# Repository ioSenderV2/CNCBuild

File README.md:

# CNCBuild

The machine, and everything about building, wiring, configuring and instrumenting it. Gantry beams are
**stacked pairs of 8020 `30-6060`** on HGR20 rails and 1605 ball screws.

Written down because these facts kept getting re-derived in conversation - travels, plate dimensions,
what shares a drag chain, which stored setting disagreed with the machine. A firmware fork's scratch
folder was the wrong home for them.

| Folder | What is in it |
|---|---|
| [`machine/`](machine) | The build itself: extrusions, rails, screws, plates, and the mechanical decisions with their reasons |
| [`linear-encoder/`](linear-encoder) | Magnetic linear scales + AS5311 + ESP32-S3 → CAN → grblHAL. The most developed subsystem; design complete, nothing built |
| [`commissioning/`](commissioning) | Measurements taken **from the machine** - travels, squaring, tape extents. The authority when the config disagrees |
| [`wiring/`](wiring) | How the boxes connect - the DB37 between the controller box and the remote axis breakout box |

## Generated views - regenerate, never edit

Three files are built from the prose rather than maintained beside it, because a
hand-maintained summary drifts from what it summarises. That is not hypothetical here: on
2026-10-02 two settled decisions were relitigated, both because a pointer had gone stale.

| Build it with | What you get |
|---|---|
| **`tools\regen.ps1`** | **everything derived, in dependency order, ending with `CNC Build.zip`.** The registry check first, then VALUES/registry.html/fusion CSV, fasteners, the cut list, the 3D model, the shop pack tallies, STATUS and INDEX, the four checkers, then the PDFs - and `make-pdf` bundles the zip on a clean print. `-NoPdf` stops after the checkers and says plainly that the PDFs and the zip are then stale. **This is the one to run**; the rows below are what it calls |
| `python tools/status.py all` | [`STATUS.md`](STATUS.md) - every open item, harvested from the SETTLED: OPEN: FLAG: REJECTED: markers in the prose. [`INDEX.md`](INDEX.md) - every heading in the repo |
| `tools\make-pdf.ps1` | **`docs/build-document.pdf`** - the whole mechanical design as one printable file: the thirteen `machine/*.md` files in reading order, a clickable contents, all fifteen photographs embedded with their captions, and links into the shop pack. ~4.4 MB, 97 pages. **Untracked** - rebuild it, do not commit it |

**If a generated file and a `.md` file disagree, the `.md` file wins** and the generated copy
is stale. The PDF needs two packages - `python -m pip install markdown pillow` - the first to
render the prose, the second to scale the photographs to print size on the way in (22.9 MB of
originals become 4.4 MB of PDF, still over 300 dpi at the size they are printed; the originals
in `machine/photos/` are never touched). `status.py` is stdlib-only on purpose, because it
gates correctness and the PDF does not.

## What lives elsewhere

| | Where | Why |
|---|---|---|
| grblHAL firmware + the CAN plugin | `stevenrwood/iMXRT1062`, branch `srw/local-build-config` | It is firmware and needs that build tree |
| ioSender (the sender application) | `ioSenderV2/ioSender` | Its own product |

## A standing rule for this repo

**The machine is the authority, not the configuration.** `$130` once read 889 mm against a real 860 mm,
because a catalog preset overwrote a measured value - which quietly cost soft-limit protection until it
was found by accident. Anything in `commissioning/` is measured; anything quoted from a config file is
labelled as such.

Datasheets are **committed, not linked**. The ESP32 module's header pinout was extracted once, lost, and
had to be recovered from a schematic - and both of that vendor's URLs refuse a plain fetch. A link is not
a copy.

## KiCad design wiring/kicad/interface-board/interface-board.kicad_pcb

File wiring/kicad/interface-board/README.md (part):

# Interface board - KiCad

The termination board that replaces the DB37 breakout: machine cables in through the
enclosure lid, RP23U5XBB controller fed out the other side. All connectors, no actives -
the 12 V arrives regulated from **its own mains-fed 12 V supply**, on the fourth pair off
the E-stop contactor's block. See
[`../../cabinet-power-and-grounding.md`](../../cabinet-power-and-grounding.md).

> FLAG: **NOT a 36 V -> 12 V buck.** This line said so until 2026-11-05 and it was wrong
> in a way nothing on the board shows: a buck off the motor rail ties logic ground to the
> motor return and throws away the drives' measured per-signal isolation. The board's
> 12 V input connector does not care where the 12 V comes from, so **nothing ordered is
> affected** - only what gets wired into it.

| File | |
|---|---|
| `interface-board.kicad_sch` | The schematic. Symbols are **embedded** (`lib_symbols`), so it needs no external libraries. |
| `interface-board.kicad_pcb` | **REV B, this branch: 133 x 132 mm, FOUR layers** - F.Cu signal, In1.Cu solid GND plane, In2.Cu solid +12V plane, B.Cu signal, plus the 36 V pours. 27.2 sq in. **Top half MACHINE IN, bottom half RP23 OUT.** The lid gets cut to match the board. The four M3 holes are **at the corners** - 22,4 / 125,4 / 5,127.3 / 127,127.3 from the top-left; [`../../../docs/drawings/board-mounting.html`](../../../docs/drawings/board-mounting.html) is the drilling drawing and regenerates from this file. **main still holds Rev A** (210 x 94, 2 layers) - the boards in hand. |
| `interface-board.pretty/` | Project footprints for the two parts KiCad's libraries lack: the 85508 jack and the 3P single-row header, both taken from the committed Molex drawings. |
| `route.py` | Regenerates ALL copper from the placed footprints - the Rev B rewrite of the channel router. Owns every track on the board; re-run it after moving a part, then refill zones via the DRC command below. GND and +12V are inner-plane zones and route themselves (every pad on both nets is through-hole); signals run as F.Cu verticals into three packed B.Cu lane corridors. Verticals cross a connector row on searched columns, 0.70 mm apart - track-past-via, not just track-track - with jogs in the gap above the row. |
| `fab/oshpark/` | Manufacturing outputs for **OSH Park**: gerbers (Protel extensions), Excellon drill, and `interface-board-oshpark.zip` - the one file their upload takes. Board is 210 x 94, 2 layers; their standard 1.6 mm matches the 85508 jack's 1.57 tooling. **Rev A ordered 2026-11-03**, OSH Park order xPBWS3rt, $164.95 for 3 with FedEx 2 Day - this zip is what was uploaded; invoice alongside. Regenerate after any board change with the two kicad-cli export commands, then re-zip. |
| `fab/oshpark-revb/` | **Rev B manufacturing outputs - FOR A QUOTE, NOT AN ORDER.** `interface-board-revb-oshpark.zip` is the single file their upload takes: 13 files, all four copper layers (`.gtl` `.g1` `.g2` `.gbl`), masks, silks, `.gm1` outline and the Excellon drill. The drill **map** is written alongside but deliberately kept **out of the zip** - it is a `.gbr` and their uploader can mistake it for a copper layer. Outline measured from the plotted gerber: **x 5..138 by y 5..137 - 133.00 x 132.00 mm, 27.2 sq in.** Regenerate after any board change **with `make-fab-revb.ps1`**, which keeps the refill and the map-exclusion from being forgotten. **Rev A's order record in `fab/oshpark/` is not touched by this.** |
| `silk.py` | Regenerates every free silkscreen label (function names, per-terminal signal names). Owns all board text - edit its tables, not the board. |
| `interface-board.kicad_pro` | Project wrapper. |
| `netlist.txt` | The connection list. **Generated from the routed board by `make-netlist.py`** - not hand-kept, and not from the seed. |
| `make-netlist.py` | Writes `netlist.txt` from the board. Run after any net change. |
| `make-fab-revb.ps1` | Builds the whole Rev B quote package - DRC with refill, both exports, the zip. Refuses to build if DRC is not clean. Run this rather than the export commands by hand. |
| `swap-power-connectors.py` | Placed the three cabinet power feeds as Mini-Fit Jr. Kept because it carries the courtyard arithmetic for row A, which is the tightest row on the board. |
| `generate.py` | **The seed that produced the first version - not the live source once KiCad has touched the file.** See the warning below. |

> FLAG: **`generate.py` is a SEED, not the source of truth once the schematic has been
> opened and re-saved by KiCad.** Re-running it overwrites hand edits and layout work.
> Same rule as the two linear-encoder boards. If the design changes, edit in Eeschema.
>
> FLAG: **AND `netlist.txt` IS NO LONGER ITS OUTPUT.** It used to be, which meant the
> only way to refresh the netlist was to run the seed - which would have destroyed the
> board. So it was hand-edited instead, and had already lost its trailer that way.
> `make-netlist.py` now derives it from the routed board, and
> `drc --schematic-parity` is what makes "from the board" and "from the schematic" the
> same statement.

## What is on it

| Machine side (top-entry, through the lid) | Controller side |
|---|---|
| 5x RJ45 vertical, one cat6 per stepper - column order **X, Y1, Y2, Z, B**, each with its limit 3P stacked below it | 2x10 IDC ribbon to RP23 **J20** (pin-for-pin), right end of the board |
| Mini-Fit Jr 3P - 3D probe (12 V), 3P - toolsetter (12 V) | 2x3 IDC ribbon to RP23 **J24** servo alarms, left end |
| 2x Mini-Fit Jr 2P - touch probes | Mini-Fit Jr 2P - 12 V IN, Mini-Fit Jr 2P - 12 V OUT to the RP23, Mini-Fit Jr **4P - 36 V IN from the supply, both legs doubled** - the three cabinet feeds side by side, all latched so a pulled feed has no bare conductor |
| **5x Mini-Fit Jr 2P - stepper power**, one per axis under its limit connector: where the **18/2** motor supply cable terminates. Pin 1 **+36 V**, pin 2 **return** | |
| 2x Mini-Fit Jr 2P - mist, flood | 3.5 mm TBs, one position per signal with silk names: limits 5P, spindle 4P, probe + door 2P |
| Mini-Fit Jr 4P - spindle (Enable, GND, GND, 0-10 V) | 3.5 mm TBs passing the new inputs through: mist 2P, flood 2P, control 4P; UART1 leaves on a **1x4 2.54 mm header** - dupont jumpers straight to the RP23's 4-pin UART header |
| Mini-Fit Jr 4P - cycle start / feed hold / e-stop / spare | 5x 2.54 mm header, **GND / Step / Dir / Enable** per axis - jumper to a Teensy T41U5XBB instead of the ribbon |
| Mini-Fit Jr 4P - UART1 for CAN, **TX / RX / 3.3V / GND** | |

**Y1 drives the controller's Y, Y2 drives A.** The three touch/3D probe signals are
wired-OR onto one PROBE net; the toolsetter goes to DOOR. Mist, flood, control and
UART1 pass straight through, connector to output terminal, position for position -
UART1's output being the 1x4 header rather than a screw block.

**RJ45 pin map** (striped conductor = signal, solid = return):
1 Step, 3 Enable, 5 Dir, 7 Alarm; evens GND. Step and Alarm sit on opposite edges of
the jack - Step is the aggressor and Alarm feeds EStop. Signals on odds is correct on
the twists by construction: in T568 every odd pin's twist partner is an even pin.

**"Evens GND" does not say WHICH even pin, and that is where a split pair comes from.**
The twists are **1-2, 3-6, 4-5, 7-8**. So each signal's return leg must land on its
own twist partner: Step 1-2, Enable **3-6**, Dir **5-4**, Alarm 7-8. Wiring it as the
numbers read - 3 with 4, 5 with 6 - puts Enable and Dir in each other's twists. The
board cannot catch it, because all four evens are the same GND net: it passes
continuity and works, and costs only signal integrity. Drive-end terminals and the
reasoning are in [`../../ig57-drives.md`](../../ig57-drives.md).

**3P pin order**: 1 = 12 V, 2 = signal, 3 = GND - matches the SN04's brown/black/blue.

🔴 **THE 36 V PAIR IS ISOLATED AND MUST STAY THAT WAY.** `+36V` and `36V_RET`
touch nothing else on the board - not GND, not +12V. That is the same rule the
12 V supply exists to protect: tying the motor return to logic ground throws away
the drives' measured per-signal isolation. **The 36 V return is not a ground.**

**THIS BOARD HAS NO PE CONNECTION AT ALL, AND THAT IS DELIBERATE.** There is no earth
or chassis net on it - 44 nets, none of them PE - **all four mounting holes are
unplated NPTH with no net**, and its enclosure is 3D printed, so there is no chassis
to bond. **Its GND arrives on one pad, J18.2 of the 12 V IN connector**, and leaves on
J19.2 to the RP23. The In1 plane distributes it from there.

✅ **THE TWO RULES ARE THE SAME RULE: SEPARATE EVERYWHERE, JOINED AT ONE POINT.** Logic
GND and the 36 V return do meet - **back at the cabinet's PE bar**, which carries
*12 V supply 0 V* and *motor supply 0 V* as two of its eight named conductors, see
[`../../cabinet-power-and-grounding.md`](../../cabinet-power-and-grounding.md).
**That bar is the single point, and the board staying isolated is what keeps it
single.** A second meeting anywhere - a jumper here, a shared terminal out at a
drive - turns one bond into a loop and puts chopped motor return current through
the logic ground plane. 🔴 **So do not "helpfully" tie `36V_RET` to GND anywhere.**

**The 36 V bus is copper pours, not traces, and that is what set the board size.**
The supply is 600 W at 36 V - **16.5 A across all axes**, nameplate, see
[`../../breakout-box.md`](../../breakout-box.md) - and 16.5 A wants about 10 mm of
1 oz copper per leg. Under the limit row **both legs are on B.Cu**, stacked, because
F.Cu in that band belongs to the five signal bundle streets that have to cross it;
down the east edge **+36V takes F.Cu and 36V_RET takes B.Cu** in one 10.2 mm channel,
stitched with 20 vias where +36V changes layer. [`route.py`](route.py) owns all of it.

**J20 is a skipped reference.** On this bench "J20" means the RP23's stepper header;
two J20s in one enclosure invites miswiring.

## Status: verified against KiCad 10.0.5

| Check | Result |
|---|---|
| ERC, error severity | **0 violations** |
| `netlist.txt` | **All 44 nets**, planes included, written straight from the kicad-cli export. FLAG: **this is no longer an independent check.** It was one while `generate.py` produced both; now that KiCad owns the schematic the file can only be derived from it, so it is documentation, not corroboration. |
| PCB DRC with schematic parity, error severity | **0 violations, 0 unconnected, 0 parity issues** |

Reproduce with:

```
kicad-cli sch erc --severity-error --exit-code-violations interface-board.kicad_sch
kicad-cli sch export netlist --format kicadsexpr --output kicad-export.net interface-board.kicad_sch
kicad-cli pcb drc --schematic-parity --severity-error --exit-code-violations --refill-zones --save-board interface-board.kicad_pcb
```

## Open items

1. **J17 alarm pin -> RP23 LED mapping.** All five alarm pins join one net on the RP23,
   so the wiring works regardless; which pin lights which axis LED is unlabelled in the
   RP23 schematic. Read the board silkscreen when making the ribbon.
2. **Footprints.** All 41 assigned and the board is placed and routed. The IDC headers
   are the standard shrouded 2.54 mm pattern (any vendor fits); the signal terminal
   blocks are 3.5 mm on the 4Ucon pattern (KF350 class fits), and the **three cabinet
   power feeds** - 12 V in, 12 V out and 36 V in - are **Mini-Fit Jr**, the same family
   as the five stepper power jacks above them. Board-side parts:

   | Position | Part | Qty |
   |---|---|---|
   | RJ45 vertical (J1-J5) | Molex **85508-5001** - top entry, THT, Cat5e, shielded (tab to GND; the patch cables are UTP so it carries nothing), no magnetics, 16.85 mm tall. 10 ordered 2026-11-03, Mouser order 40971773. NOT the sensor board's jack - that stays the unshielded 69255-004LF, whose end must float | 5 |
   | 3P single row (J6-J12) | Molex **39-30-1039** - 5566, vertical, peg lock. 20 ordered 2026-11-03, Mouser order 40971773 | 7 |
   | 4P dual row 2x2 (J15, J32, J33, **J55 36 V in**) | Molex **46999-0621** - 2x2 vertical, tin, 10 ordered 2026-11-02, Mouser order 40971389. **J55 is the 36 V input and uses all four circuits for two conductors**: pins 1+2 are both `+36V`, pins 3+4 are both `36V_RET`. Two crimps per leg in the cable, not one | 4 |
   | 2P dual row (J13, J14, J30, J31, **J18 12 V in, J19 12 V out**, **J50-J54 stepper power**) | Molex **39-29-9027** - 2 ckt vertical with peg, tin, 10 ordered 2026-11-02, Mouser order 40971389 (the same order's 39-31-0027 is 10 spare 2-ckt without peg - they also fit these footprints). The four probe/mist/flood positions carry signal; **the five power positions carry 5 A each** - Mini-Fit Jr is rated 9 A on 18 AWG, so the part is the same and the crimp terminal is what must suit the wire. **11 positions against 10 pegged parts in hand** - covered by the 10 pegless 39-31-0027 from the same order, which fit this footprint; the peg is worth keeping on the feeds that get unplugged | 11 |
   | 3.5 mm TB 2P (J23, J34, J35) | KF350-class screw block, 4Ucon pattern - **to order** | 3 |
   | 3.5 mm TB 4P (J22, J36) | same family - **to order** | 2 |
   | 3.5 mm TB 5P (J21) | same family - **to order** | 1 |
   | Pin header 1x04 2.54 mm (J40-J44, J37 UART1 out) | any breakaway header - **to order or from stock** | 6 |

   Cable-end housings (5557, take the 5556 terminals already in stock): 3P single row
   **39-01-4031**, 4P single row **39-01-4041**, 2P dual row **39-01-2025** family.
   There is no 2P in the 5566 single-row range - it starts at 3 circuits, which is why
   the touch probes are dual-row and self-key by shape against the 3P sockets.

   NOTE: **THE THREE CABINET FEEDS NOW NEED CABLE-END HOUSINGS, WHICH SCREW BLOCKS DID
   NOT.** Two more 2P dual-row for the 12 V pair and one more 4P for the 36 V input -
   and the 36 V one takes **four** crimp terminals for its two conductors. That is the
   ordering consequence of the connector change and it is the only one.
3. **RP23 header state, from his board in hand:** J24 already carries a bare 2x3 header;
   J20 is open with plenty of room, so it gets a **shrouded** 2x10 (Digi-Key: CNC Tech /
   On Shore class, 2.54 mm vertical THT). The alarm ribbon's RP23 end therefore lands on
   an unkeyed header - mark pin 1 against the silkscreen; this board's J17 can still be
   shrouded so the interface end is foolproof.

---

## Rev B - designed on this branch, 2026-11-09

**His call, 2026-11-09: "proceed with this alternate design and see how it shakes out."**
This branch is that design, done: placed, routed, ERC/DRC clean, silkscreened, mounting
sheet regenerated. 🔴 **THE FAB STILL WAITS** until Rev A's lessons are in - no order goes
out on the back of this branch alone.

### What it came out as

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
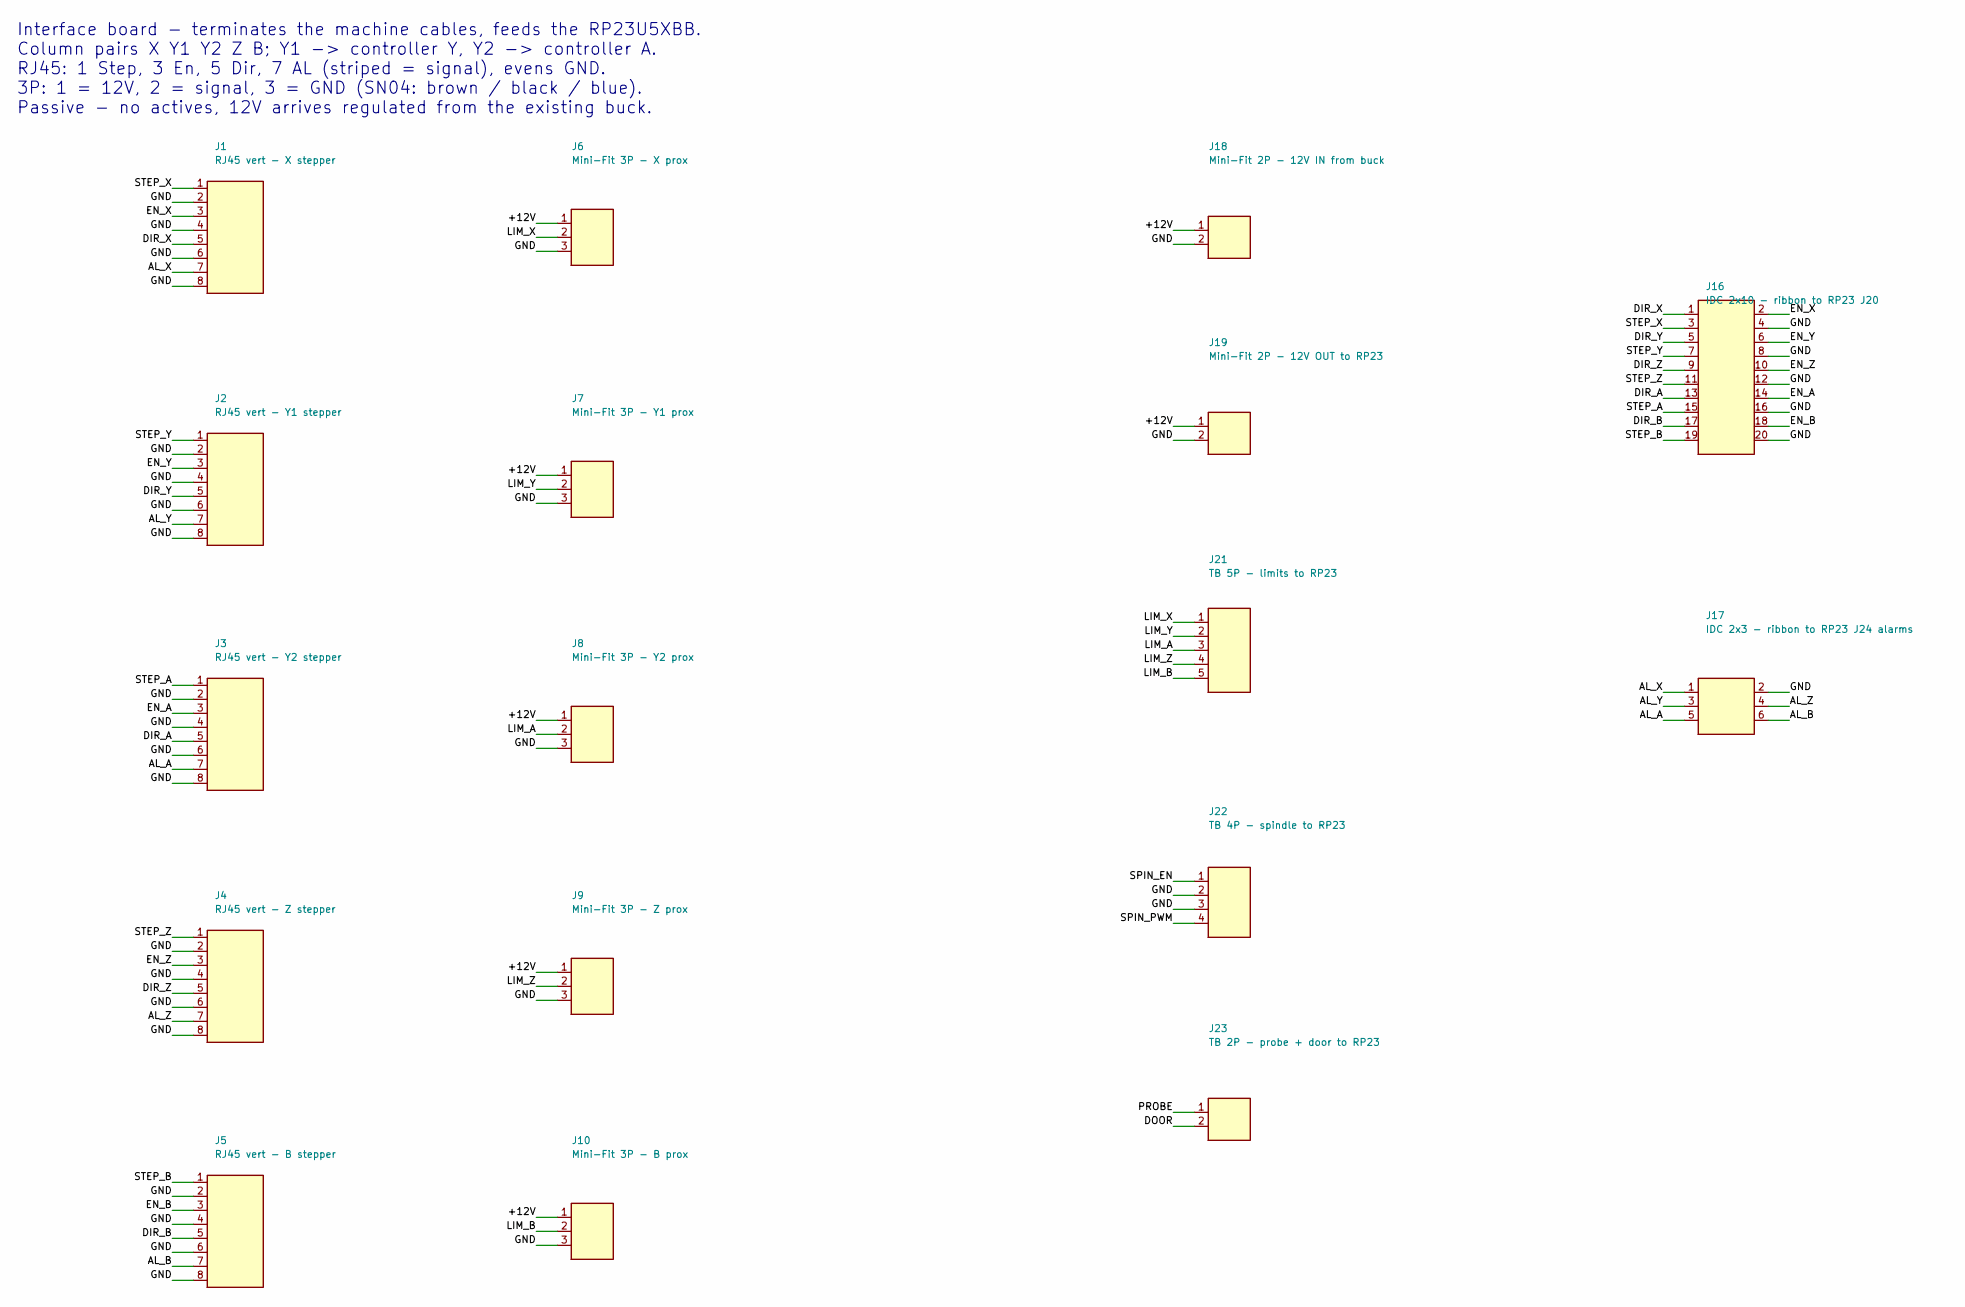
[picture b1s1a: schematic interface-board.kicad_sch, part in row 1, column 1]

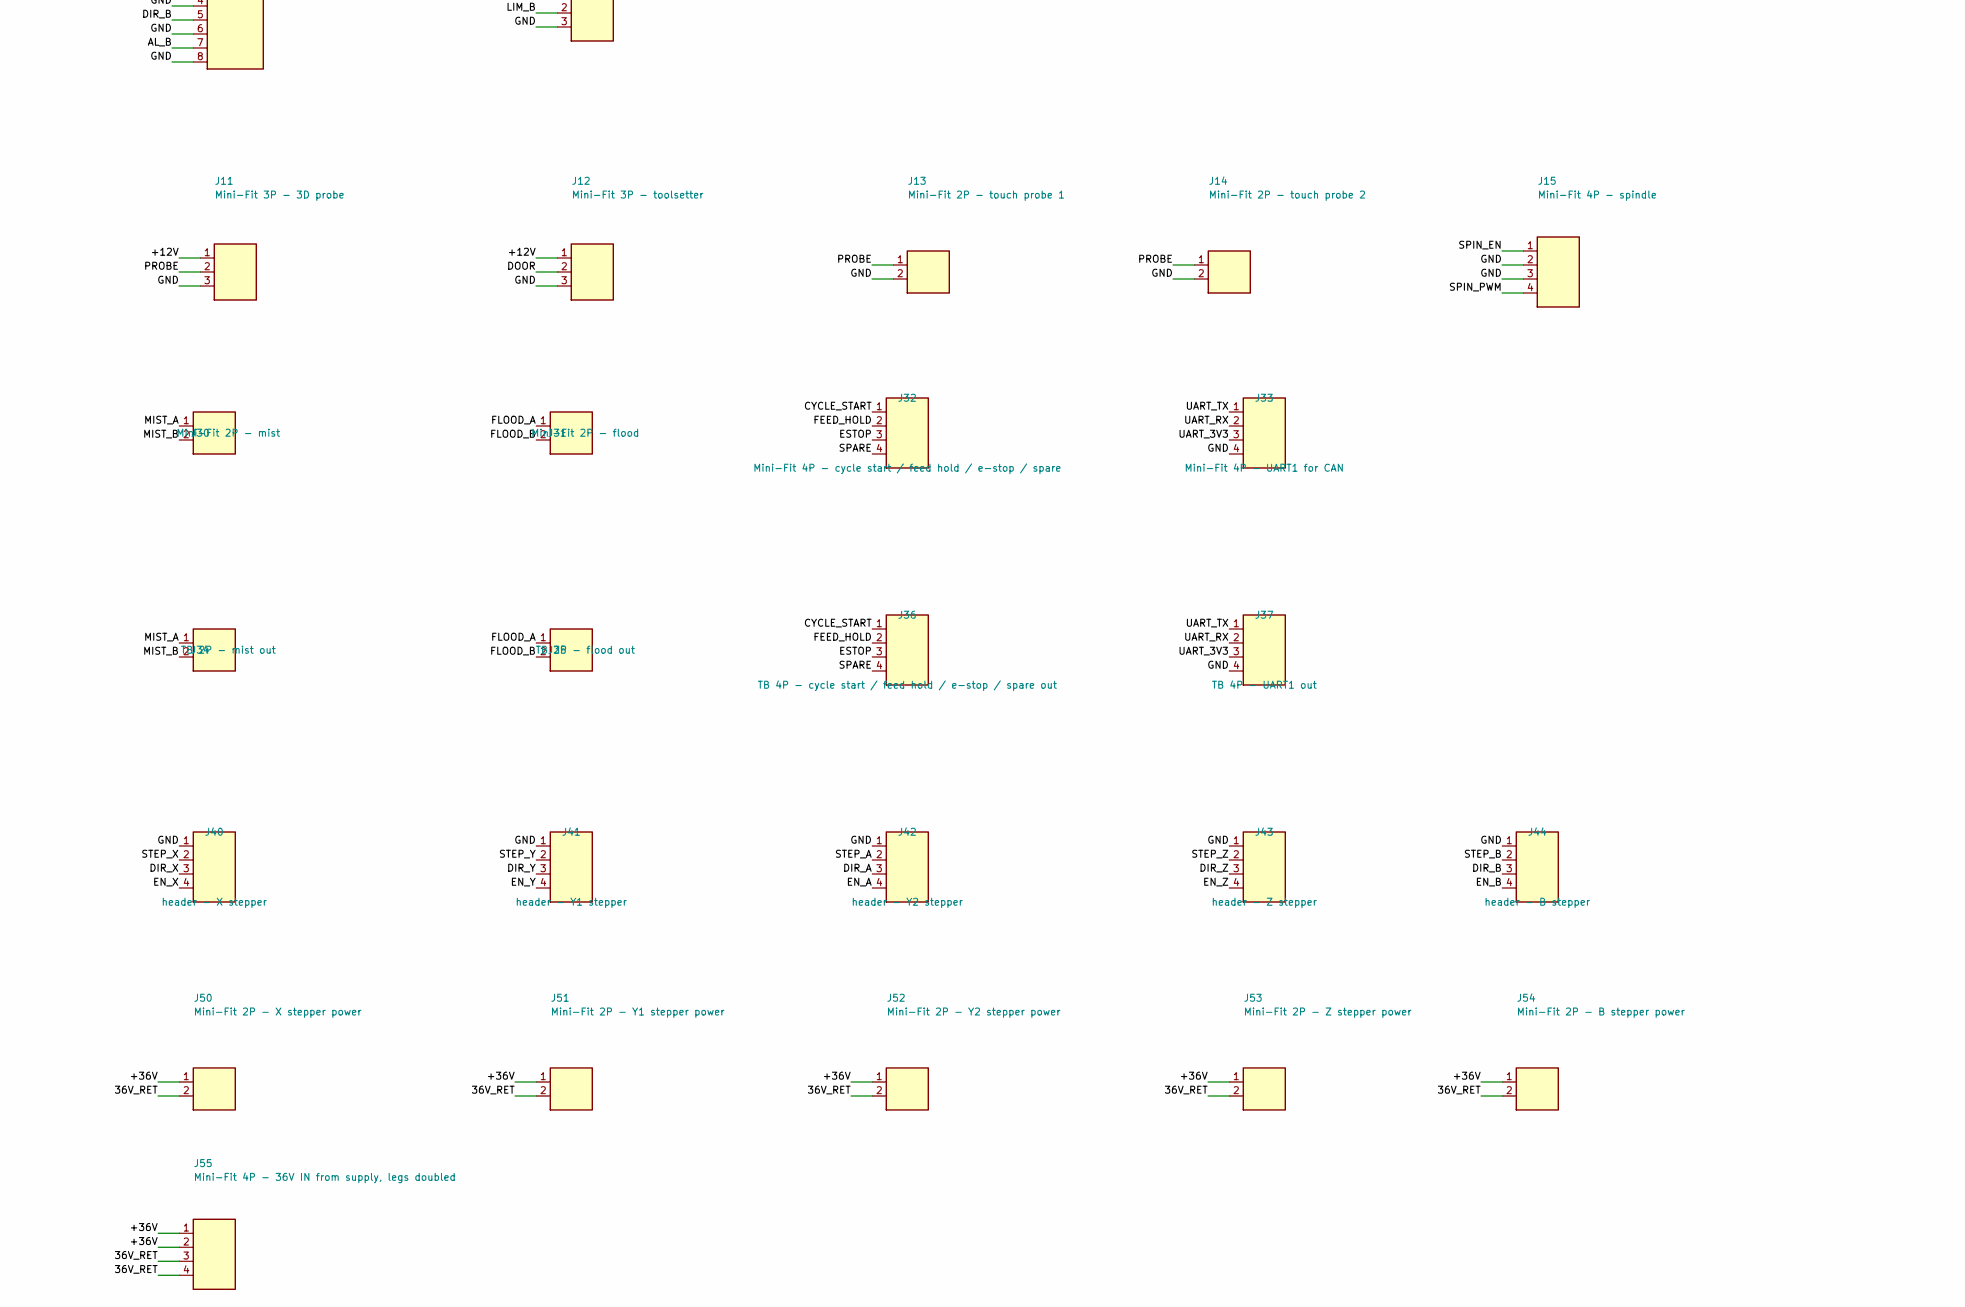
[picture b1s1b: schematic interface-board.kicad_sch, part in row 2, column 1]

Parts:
J1: RJ45 vert - X stepper; RJ45_Molex_85508-5001_Vertical
J2: RJ45 vert - Y1 stepper; RJ45_Molex_85508-5001_Vertical
J3: RJ45 vert - Y2 stepper; RJ45_Molex_85508-5001_Vertical
J4: RJ45 vert - Z stepper; RJ45_Molex_85508-5001_Vertical
J5: RJ45 vert - B stepper; RJ45_Molex_85508-5001_Vertical
J6: Mini-Fit 3P - X prox; Molex_Mini-Fit_Jr_5566-03A3_1x03_P4.20mm_Vertical
J7: Mini-Fit 3P - Y1 prox; Molex_Mini-Fit_Jr_5566-03A3_1x03_P4.20mm_Vertical
J8: Mini-Fit 3P - Y2 prox; Molex_Mini-Fit_Jr_5566-03A3_1x03_P4.20mm_Vertical
J9: Mini-Fit 3P - Z prox; Molex_Mini-Fit_Jr_5566-03A3_1x03_P4.20mm_Vertical
J10: Mini-Fit 3P - B prox; Molex_Mini-Fit_Jr_5566-03A3_1x03_P4.20mm_Vertical
J11: Mini-Fit 3P - 3D probe; Molex_Mini-Fit_Jr_5566-03A3_1x03_P4.20mm_Vertical
J12: Mini-Fit 3P - toolsetter; Molex_Mini-Fit_Jr_5566-03A3_1x03_P4.20mm_Vertical
J13: Mini-Fit 2P - touch probe 1; Molex_Mini-Fit_Jr_5566-02A2_2x01_P4.20mm_Vertical
J14: Mini-Fit 2P - touch probe 2; Molex_Mini-Fit_Jr_5566-02A2_2x01_P4.20mm_Vertical
J15: Mini-Fit 4P - spindle; Molex_Mini-Fit_Jr_5566-04A2_2x02_P4.20mm_Vertical
J16: IDC 2x10 - ribbon to RP23 J20; IDC-Header_2x10_P2.54mm_Vertical
J17: IDC 2x3 - ribbon to RP23 J24 alarms; IDC-Header_2x03_P2.54mm_Vertical
J18: Mini-Fit 2P - 12V IN from buck; Molex_Mini-Fit_Jr_5566-02A2_2x01_P4.20mm_Vertical
J19: Mini-Fit 2P - 12V OUT to RP23; Molex_Mini-Fit_Jr_5566-02A2_2x01_P4.20mm_Vertical
J21: TB 5P - limits to RP23; TerminalBlock_4Ucon_1x05_P3.50mm_Horizontal
J22: TB 4P - spindle to RP23; TerminalBlock_4Ucon_1x04_P3.50mm_Horizontal
J23: TB 2P - probe + door to RP23; TerminalBlock_4Ucon_1x02_P3.50mm_Horizontal
J30: Mini-Fit 2P - mist; Molex_Mini-Fit_Jr_5566-02A2_2x01_P4.20mm_Vertical
J31: Mini-Fit 2P - flood; Molex_Mini-Fit_Jr_5566-02A2_2x01_P4.20mm_Vertical
J32: Mini-Fit 4P - cycle start / feed hold / e-stop / 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; Molex_Mini-Fit_Jr_5566-04A2_2x02_P4.20mm_Vertical
J33: Mini-Fit 4P - UART1 for CAN; Molex_Mini-Fit_Jr_5566-04A2_2x02_P4.20mm_Vertical
J34: TB 2P - mist out; TerminalBlock_4Ucon_1x02_P3.50mm_Horizontal
J35: TB 2P - flood out; TerminalBlock_4Ucon_1x02_P3.50mm_Horizontal
J36: TB 4P - cycle start / feed hold / e-stop / spare 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; TerminalBlock_4Ucon_1x04_P3.50mm_Horizontal
J37: TB 4P - UART1 out; PinHeader_1x04_P2.54mm_Vertical
J40: header - X stepper; PinHeader_1x04_P2.54mm_Vertical
J41: header - Y1 stepper; PinHeader_1x04_P2.54mm_Vertical
J42: header - Y2 stepper; PinHeader_1x04_P2.54mm_Vertical
J43: header - Z stepper; PinHeader_1x04_P2.54mm_Vertical
J44: header - B stepper; PinHeader_1x04_P2.54mm_Vertical
J50: Mini-Fit 2P - X stepper power; Molex_Mini-Fit_Jr_5566-02A2_2x01_P4.20mm_Vertical
J51: Mini-Fit 2P - Y1 stepper power; Molex_Mini-Fit_Jr_5566-02A2_2x01_P4.20mm_Vertical
J52: Mini-Fit 2P - Y2 stepper power; Molex_Mini-Fit_Jr_5566-02A2_2x01_P4.20mm_Vertical
J53: Mini-Fit 2P - Z stepper power; Molex_Mini-Fit_Jr_5566-02A2_2x01_P4.20mm_Vertical
J54: Mini-Fit 2P - B stepper power; Molex_Mini-Fit_Jr_5566-02A2_2x01_P4.20mm_Vertical
J55: Mini-Fit 4P - 36V IN from supply, legs doubled; Molex_Mini-Fit_Jr_5566-04A2_2x02_P4.20mm_Vertical

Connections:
36V_RET: J50.2, J51.2, J52.2, J53.2, J54.2, J55.3, J55.4
+12V: J6.1, J7.1, J8.1, J9.1, J10.1, J11.1, J12.1, J18.1, J19.1
+36V: J50.1, J51.1, J52.1, J53.1, J54.1, J55.1, J55.2
AL_A: J3.7, J17.5
AL_B: J5.7, J17.6
AL_X: J1.7, J17.1
AL_Y: J2.7, J17.3
AL_Z: J4.7, J17.4
CYCLE_START: J32.1, J36.1
DIR_A: J3.5, J16.13, J42.3
DIR_B: J5.5, J16.17, J44.3
DIR_X: J1.5, J16.1, J40.3
DIR_Y: J2.5, J16.5, J41.3
DIR_Z: J4.5, J16.9, J43.3
DOOR: J12.2, J23.2
EN_A: J3.3, J16.14, J42.4
EN_B: J5.3, J16.18, J44.4
EN_X: J1.3, J16.2, J40.4
EN_Y: J2.3, J16.6, J41.4
EN_Z: J4.3, J16.10, J43.4
ESTOP: J32.3, J36.3
FEED_HOLD: J32.2, J36.2
FLOOD_A: J31.1, J35.1
FLOOD_B: J31.2, J35.2
GND: J1.2, J1.4, J1.6, J1.8, J2.2, J2.4, J2.6, J2.8, J3.2, J3.4, J3.6, J3.8, J4.2, J4.4, J4.6, J4.8, J5.2, J5.4, J5.6, J5.8, J6.3, J7.3, J8.3, J9.3, J10.3, J11.3, J12.3, J13.2, J14.2, J15.2, J15.3, J16.4, J16.8, J16.12, J16.16, J16.20, J17.2, J18.2, J19.2, J22.2, J22.3, J33.4, J37.4, J40.1, J41.1, J42.1, J43.1, J44.1
LIM_A: J8.2, J21.3
LIM_B: J10.2, J21.5
LIM_X: J6.2, J21.1
LIM_Y: J7.2, J21.2
LIM_Z: J9.2, J21.4
MIST_A: J30.1, J34.1
MIST_B: J30.2, J34.2
PROBE: J11.2, J13.1, J14.1, J23.1
SPARE: J32.4, J36.4
SPIN_EN: J15.1, J22.1
SPIN_PWM: J15.4, J22.4
STEP_A: J3.1, J16.15, J42.2
STEP_B: J5.1, J16.19, J44.2
STEP_X: J1.1, J16.3, J40.2
STEP_Y: J2.1, J16.7, J41.2
STEP_Z: J4.1, J16.11, J43.2
UART_3V3: J33.3, J37.3
UART_RX: J33.2, J37.2
UART_TX: J33.1, J37.1

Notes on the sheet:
Interface board - terminates the machine cables, feeds the RP23U5XBB. Column pairs X Y1 Y2 Z B; Y1 -> controller Y, Y2 -> controller A. RJ45: 1 Step, 3 En, 5 Dir, 7 AL (striped = signal), evens GND. 3P: 1 = 12V, 2 = signal, 3 = GND (SN04: brown / black / blue). Passive - no actives, 12V arrives reg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

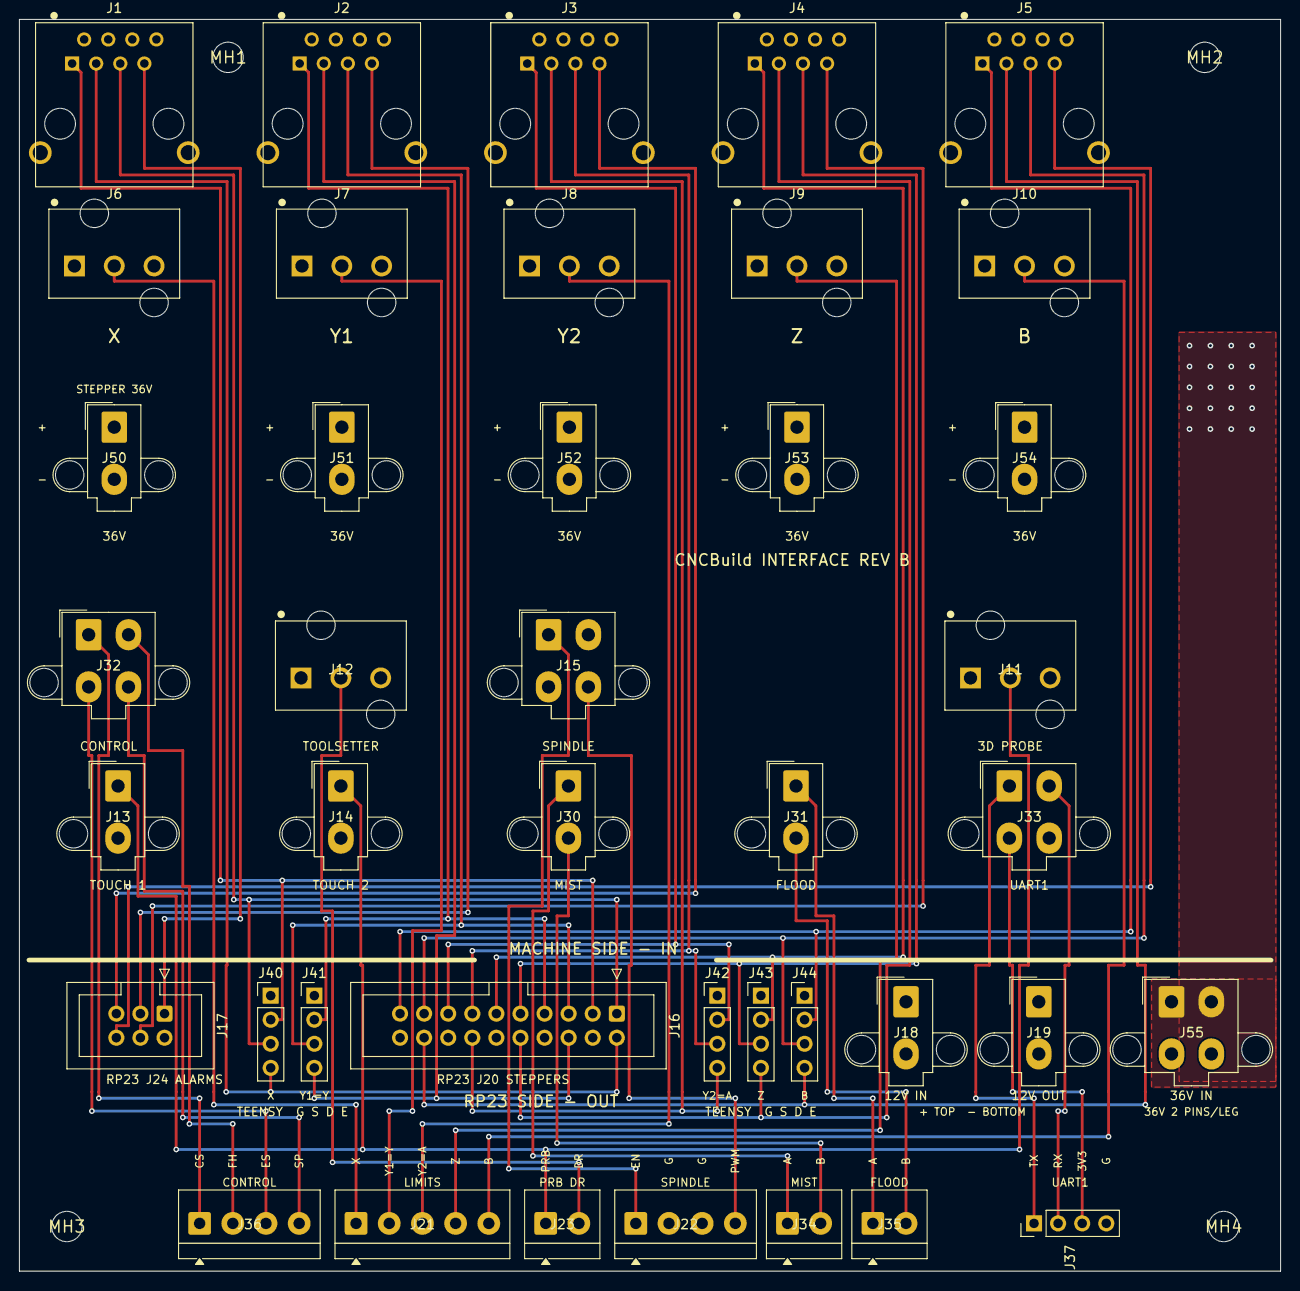
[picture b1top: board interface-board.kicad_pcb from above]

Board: 4 copper layers, 133.0 x 132.0 mm, 45 parts (0 on the bottom side), 44 nets.

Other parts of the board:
MH1, MH2, MH3, MH4: MountingHole_3.2mm

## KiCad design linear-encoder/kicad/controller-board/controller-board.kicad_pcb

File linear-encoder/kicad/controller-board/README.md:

# Controller board - KiCad

Schematic for the daughter board described in [`../../controller-board.md`](../../controller-board.md).

| File | |
|---|---|
| `controller-board.kicad_sch` | The schematic. Symbols are **embedded** (`lib_symbols`), so it needs no external libraries. |
| `controller-board.kicad_pro` | Project wrapper. |
| `netlist.txt` | The connection list, generated from the same source as the schematic. |
| `generate.py` | **The seed that produced the first version - not the live source any more.** See the warning below before re-running it. |

> FLAG: **`generate.py` is now a SEED, not the source of truth.**
> The schematic has since been **opened and re-saved by KiCad 10**, which upgraded the file format and
> may carry hand edits and layout work. **Re-running `generate.py` overwrites all of that.** Treat the
> `.kicad_sch` as the live document from here on; keep `generate.py` only as the record of how the
> netlist was derived, and if the design changes, edit in Eeschema and update `netlist.txt` to match.

## Status: verified against KiCad 10.0.5

Opened and checked with `kicad-cli`, not just written and hoped for:

| Check | Result |
|---|---|
| Parses / loads | **Yes** - `kicad-cli sch erc` and `sch export netlist` both succeed |
| Netlist matches `netlist.txt` | **Exactly.** All 15 nets, 0 mismatches, no extra or missing nodes - re-checked after KiCad re-saved the file, so connectivity survived the format upgrade |
| ERC violations | **22**, all one warning type - see below |

Reproduce with:

```
kicad-cli sch erc --severity-all --output erc-report.txt controller-board.kicad_sch
kicad-cli sch export netlist --format kicadsexpr --output kicad-export.net controller-board.kicad_sch
```

### The 22 remaining warnings are expected

All are `lib_symbol_issues`: *"The current configuration does not include the symbol library 'cnc'"*.
The symbols are embedded in the file rather than coming from a configured library, so KiCad notes it.
Nothing is broken - and the warning is arguably useful, because those symbols **are** placeholders.

An earlier run had 134 violations. The other 112 were real and are fixed:

- **107 x `endpoint_off_grid`** - placement origins were not multiples of 1.27 mm, so every pin and
  stub sat off the connection grid. Connections still resolved, but off-grid endpoints can silently
  fail to connect once a human edits the sheet. `generate.py` now snaps origins.
- **5 x `pin_not_connected`** - header pins 2 (5V), 5/7 (UART) and 6/8 (USB), which are deliberately
  unused. Now carry `no_connect` markers, which turns an error into a recorded decision.

## How it is drawn

**Connections are by net label on a short stub at each pin**, not point-to-point wires - electrically
identical for netlist and ERC purposes, and far less error-prone to generate than routing 40-odd nets
by computed coordinates. It reads as a fan-out list rather than a picture of wires, which is what the
board actually is.

## Symbols are placeholders - swap before layout

`cnc:RJ45_8`, `cnc:HDR_2x10`, `cnc:R`, `cnc:C` are minimal rectangles with correct pin numbering:
enough to carry the netlist, not real parts. Before layout, replace them with manufacturer symbols and
footprints - in particular:

- the RJ45: **shielded, NO integrated magnetics** (see the warning at the top of `controller-board.md`);
- the 2x10 header: **2.00 mm pitch**, not 2.54 mm.

`J1..J4` are X, Y, A, Z in that order; `J5` is the header to the module's `P1`.

Expect a "no power source" ERC complaint once real power symbols are used - 3V3 arrives through a
passive header pin, which is honest for a daughter board. A `PWR_FLAG` on `+3V3` and `GND` settles it.

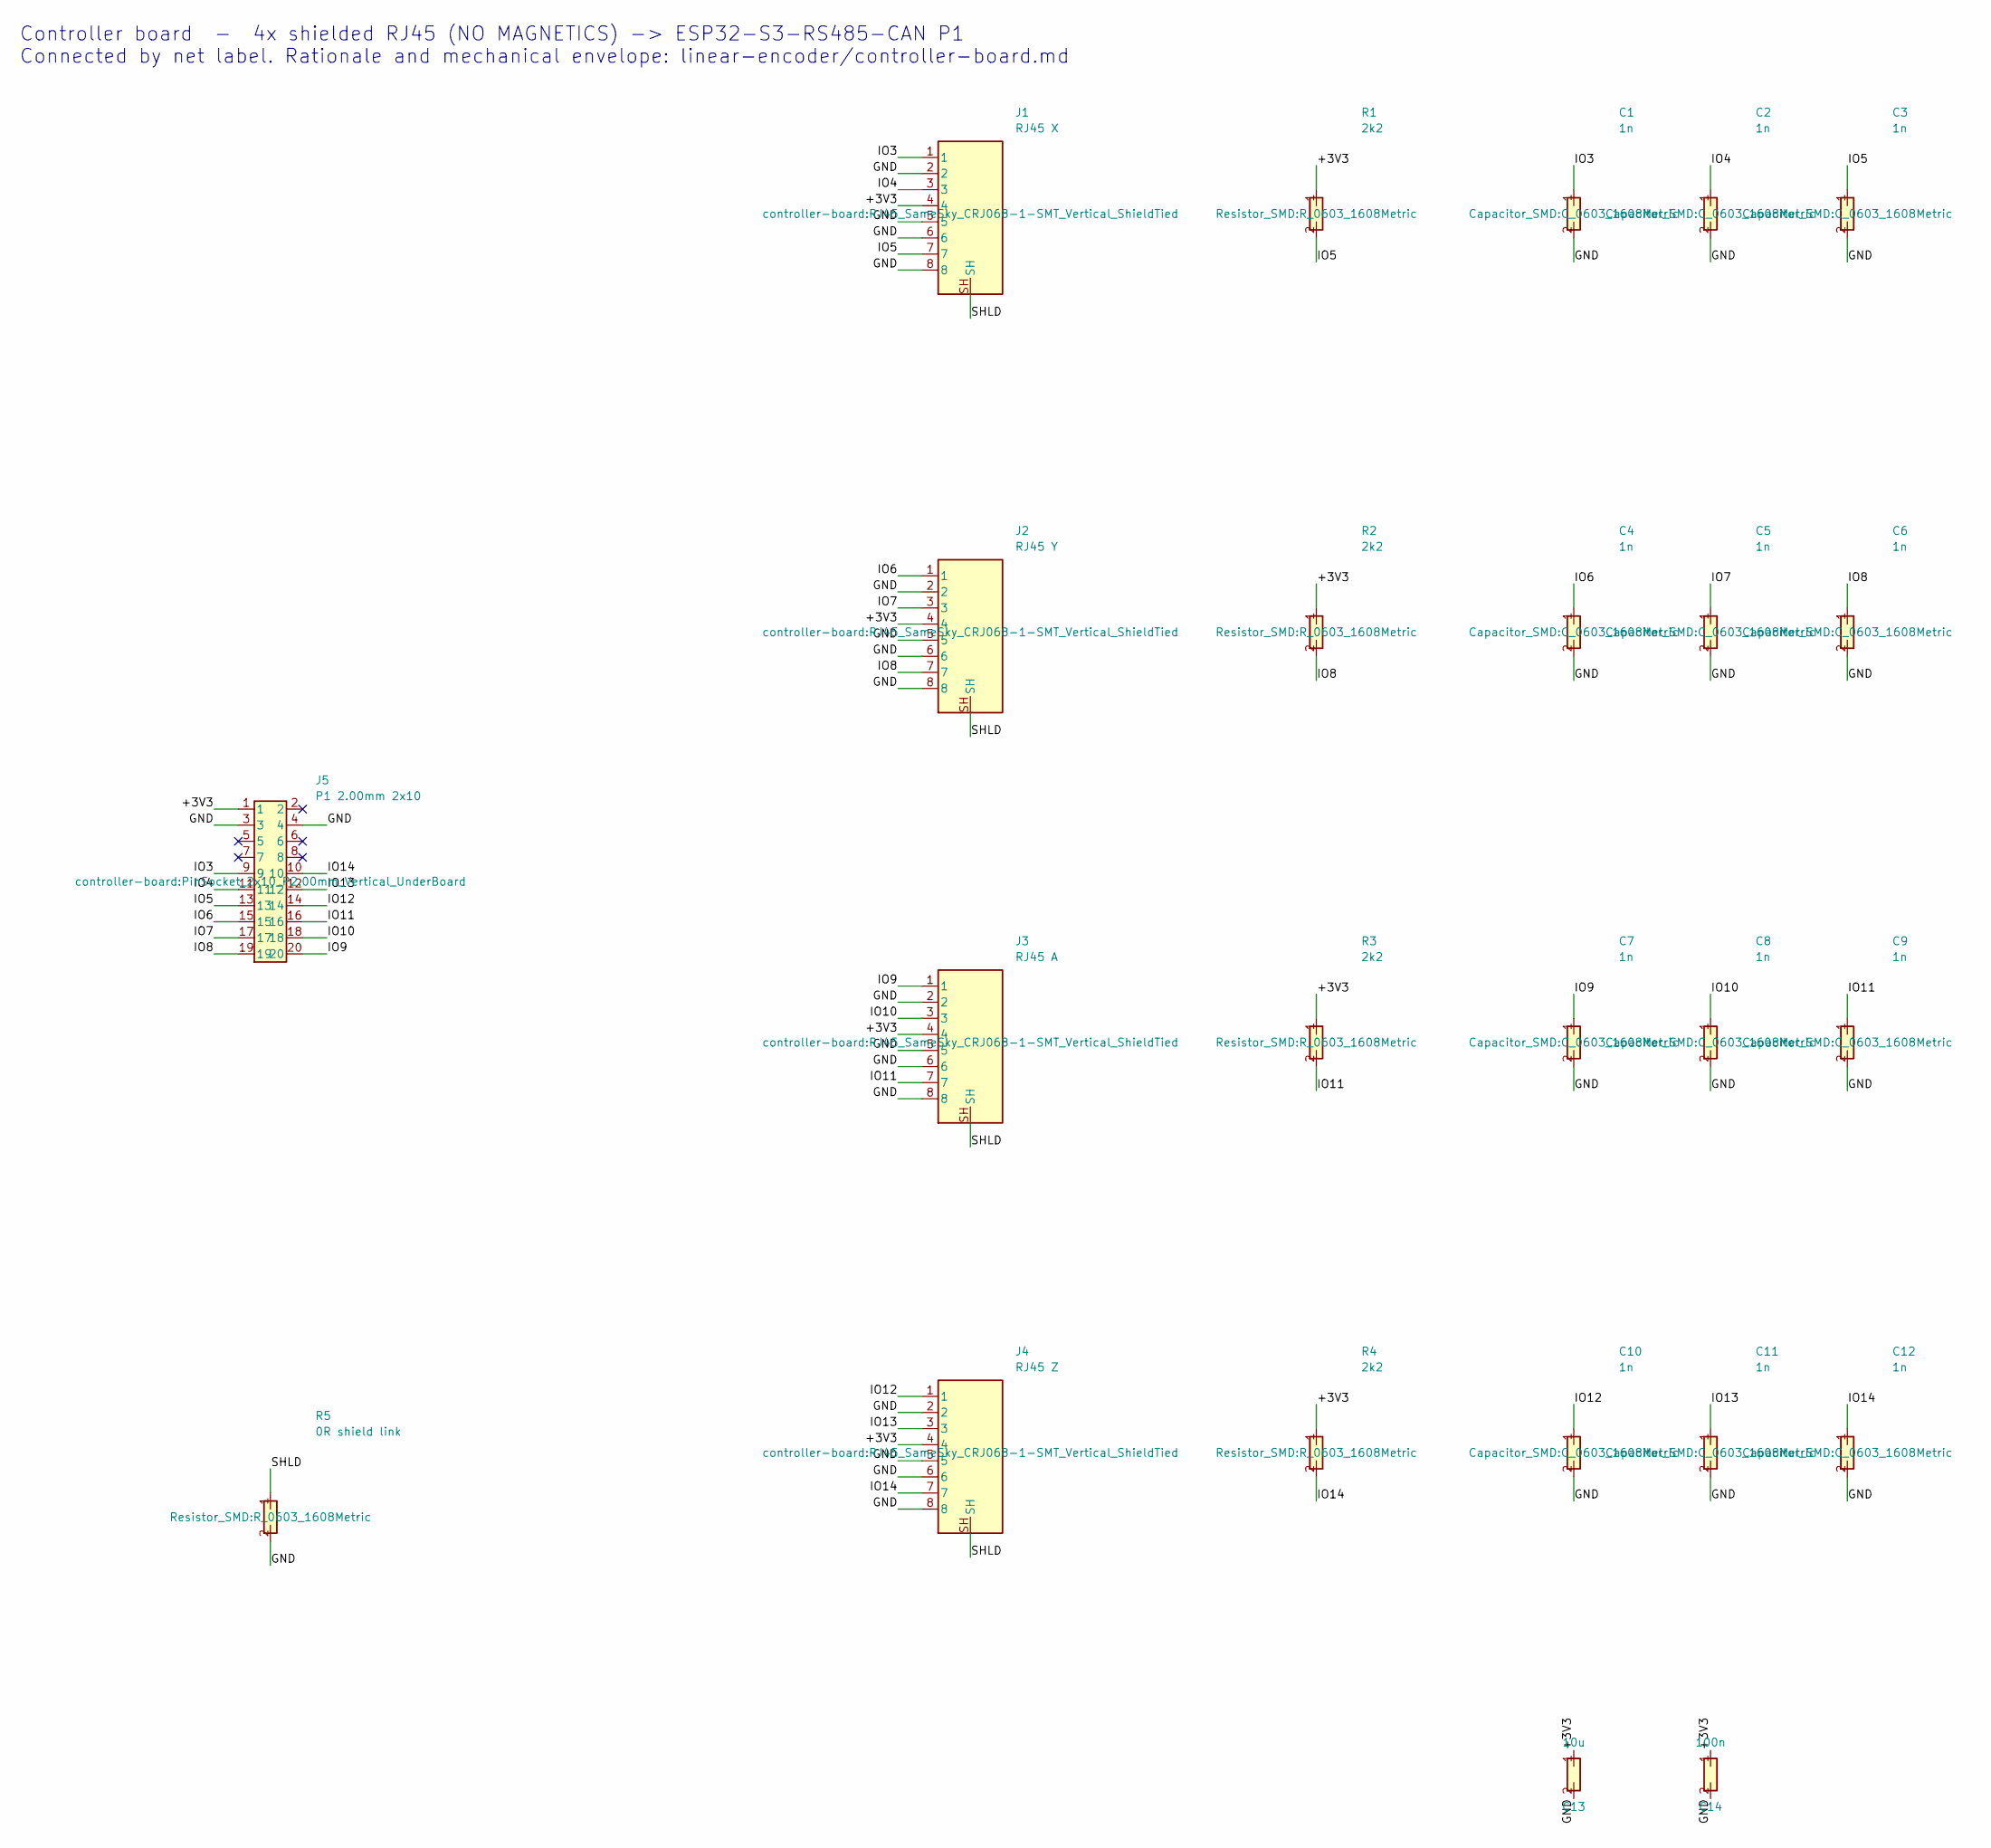
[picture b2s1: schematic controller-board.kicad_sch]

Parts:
C1, C2, C3, C4, C5, C6, C7, C8, C9, C10, C11, C12: 1n; C_0603_1608Metric
C13: 10u; C_0805_2012Metric
C14: 100n; C_0603_1608Metric
J1: RJ45 X; RJ45_SameSky_CRJ068-1-SMT_Vertical_ShieldTied
J2: RJ45 Y; RJ45_SameSky_CRJ068-1-SMT_Vertical_ShieldTied
J3: RJ45 A; RJ45_SameSky_CRJ068-1-SMT_Vertical_ShieldTied
J4: RJ45 Z; RJ45_SameSky_CRJ068-1-SMT_Vertical_ShieldTied
J5: P1 2.00mm 2x10; PinSocket_2x10_P2.00mm_Vertical_UnderBoard
R1, R2, R3, R4: 2k2; R_0603_1608Metric
R5: 0R shield link; R_0603_1608Metric

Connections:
+3V3: C13.1, C14.1, J1.4, J2.4, J3.4, J4.4, J5.1, R1.1, R2.1, R3.1, R4.1
GND: C1.2, C2.2, C3.2, C4.2, C5.2, C6.2, C7.2, C8.2, C9.2, C10.2, C11.2, C12.2, C13.2, C14.2, J1.2, J1.5, J1.6, J1.8, J2.2, J2.5, J2.6, J2.8, J3.2, J3.5, J3.6, J3.8, J4.2, J4.5, J4.6, J4.8, J5.3, J5.4, R5.2
IO3: C1.1, J1.1, J5.9
IO4: C2.1, J1.3, J5.11
IO5: C3.1, J1.7, J5.13, R1.2
IO6: C4.1, J2.1, J5.15
IO7: C5.1, J2.3, J5.17
IO8: C6.1, J2.7, J5.19, R2.2
IO9: C7.1, J3.1, J5.20
IO10: C8.1, J3.3, J5.18
IO11: C9.1, J3.7, J5.16, R3.2
IO12: C10.1, J4.1, J5.14
IO13: C11.1, J4.3, J5.12
IO14: C12.1, J4.7, J5.10, R4.2
SHLD: J1.SH, J2.SH, J3.SH, J4.SH, R5.1

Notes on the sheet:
Controller board - 4x shielded RJ45 (NO MAGNETICS) -> ESP32-S3-RS485-CAN P1 Connected by net label. Rationale and mechanical envelope: linear-encoder/controller-board.md

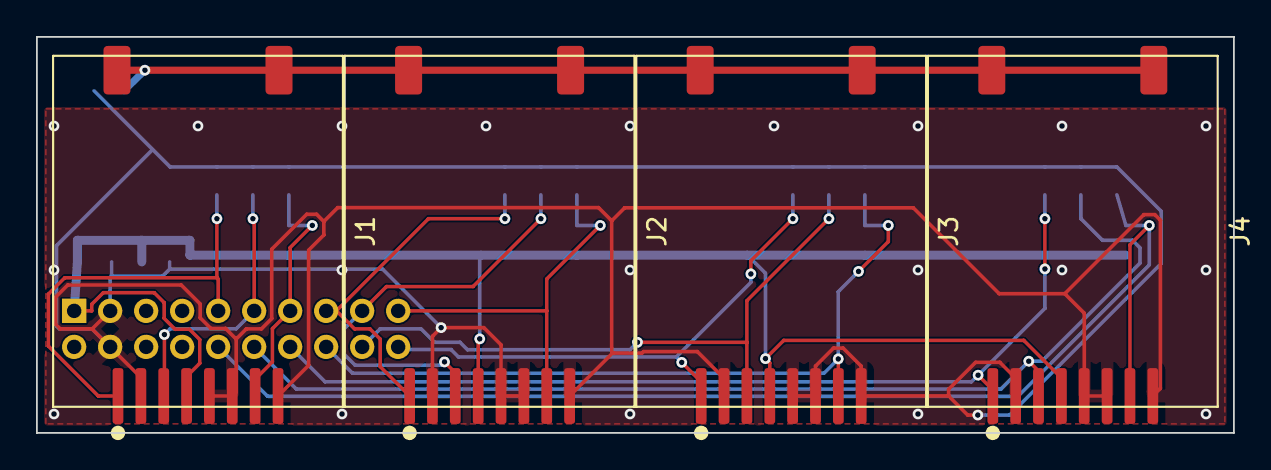
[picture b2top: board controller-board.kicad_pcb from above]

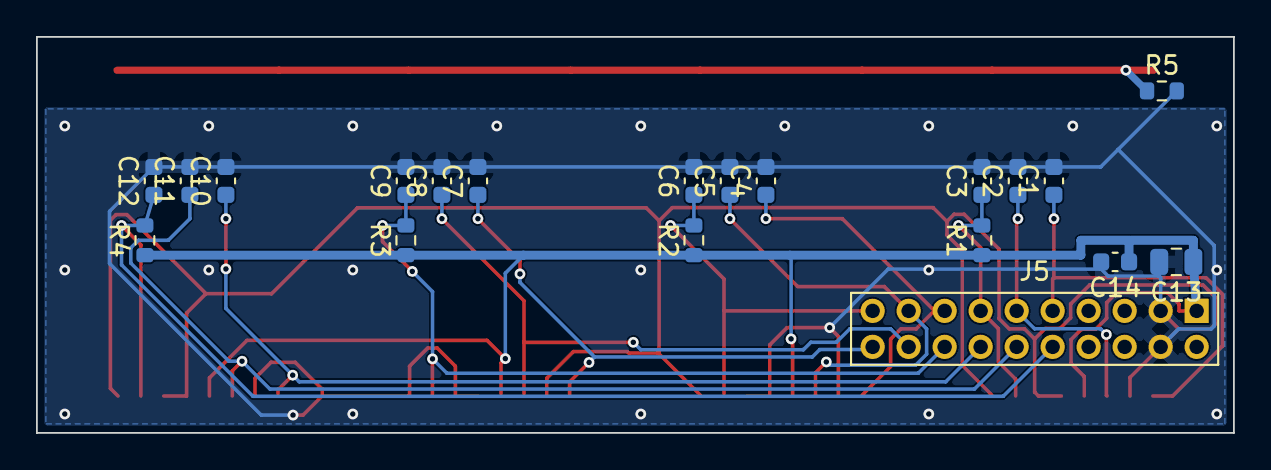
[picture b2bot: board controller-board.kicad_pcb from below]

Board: 2 copper layers, 66.5 x 22.0 mm, 24 parts (20 on the bottom side), 15 nets.

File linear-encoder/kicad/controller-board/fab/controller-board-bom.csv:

"Refs","Value","Footprint","Qty"
"C1-C12","1n","Capacitor_SMD:C_0603_1608Metric","12"
"C13","10u","Capacitor_SMD:C_0805_2012Metric","1"
"C14","100n","Capacitor_SMD:C_0603_1608Metric","1"
"J1","RJ45 X","controller-board:RJ45_SameSky_CRJ068-1-SMT_Vertical_ShieldTied","1"
"J2","RJ45 Y","controller-board:RJ45_SameSky_CRJ068-1-SMT_Vertical_ShieldTied","1"
"J3","RJ45 A","controller-board:RJ45_SameSky_CRJ068-1-SMT_Vertical_ShieldTied","1"
"J4","RJ45 Z","controller-board:RJ45_SameSky_CRJ068-1-SMT_Vertical_ShieldTied","1"
"J5","P1 2.00mm 2x10","controller-board:PinSocket_2x10_P2.00mm_Vertical_UnderBoard","1"
"R1-R4","2k2","Resistor_SMD:R_0603_1608Metric","4"
"R5","0R shield link","Resistor_SMD:R_0603_1608Metric","1"
